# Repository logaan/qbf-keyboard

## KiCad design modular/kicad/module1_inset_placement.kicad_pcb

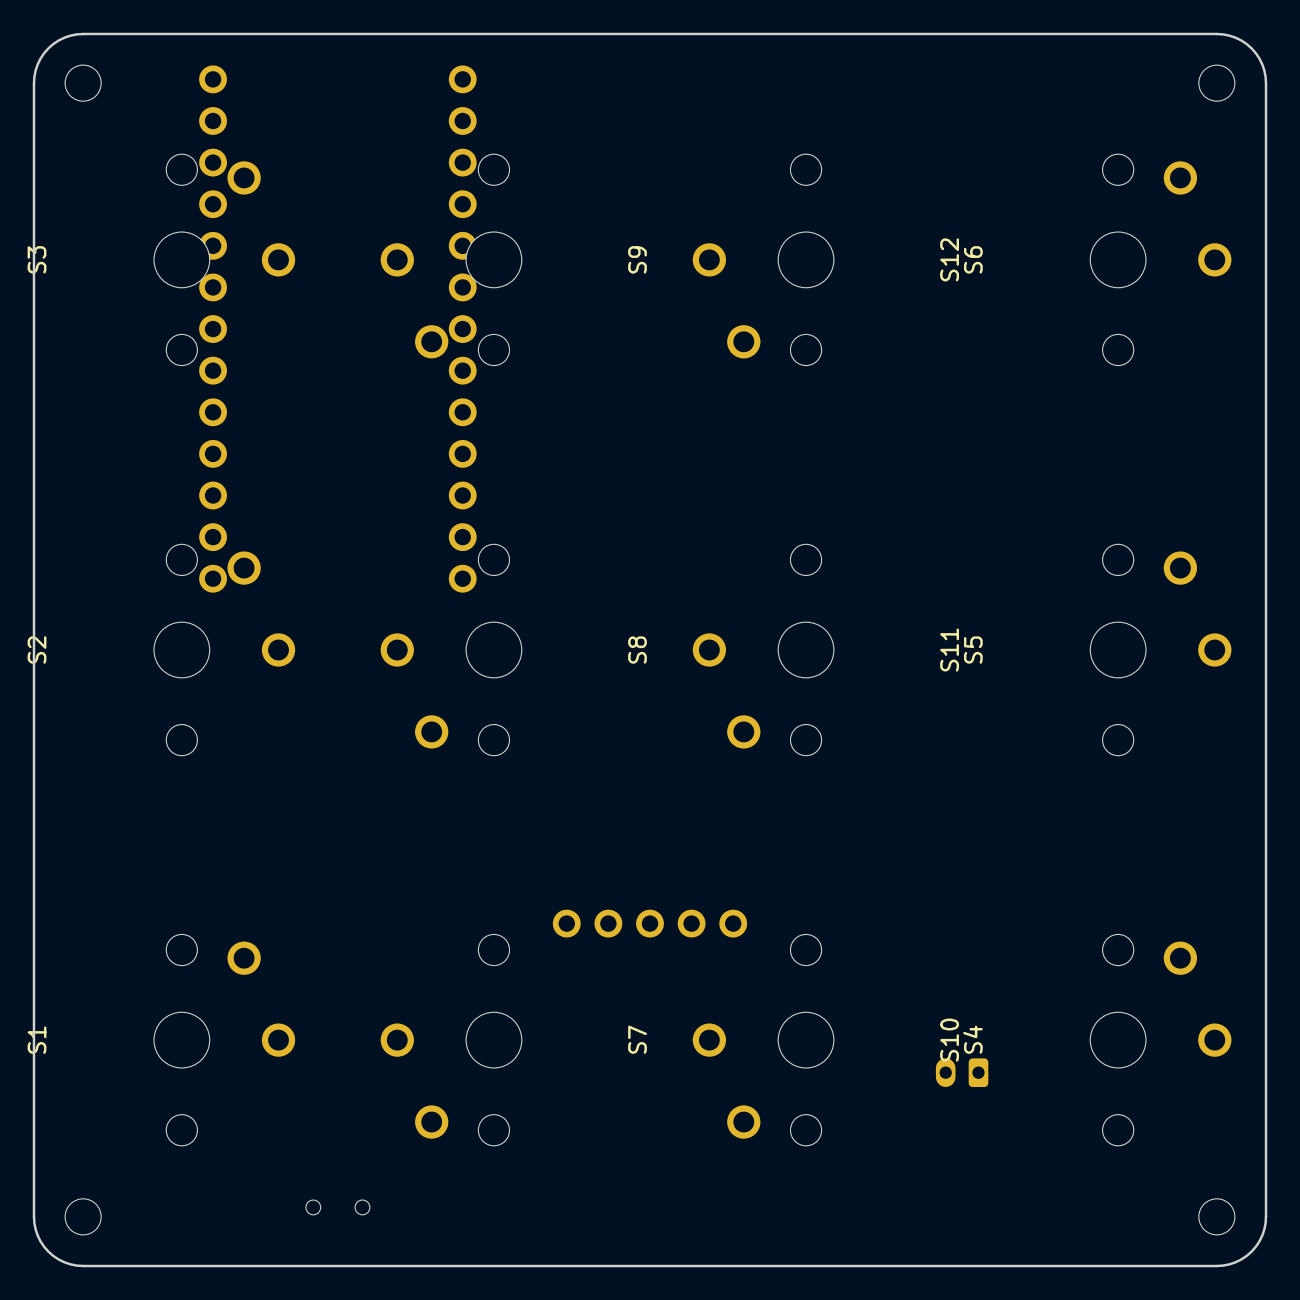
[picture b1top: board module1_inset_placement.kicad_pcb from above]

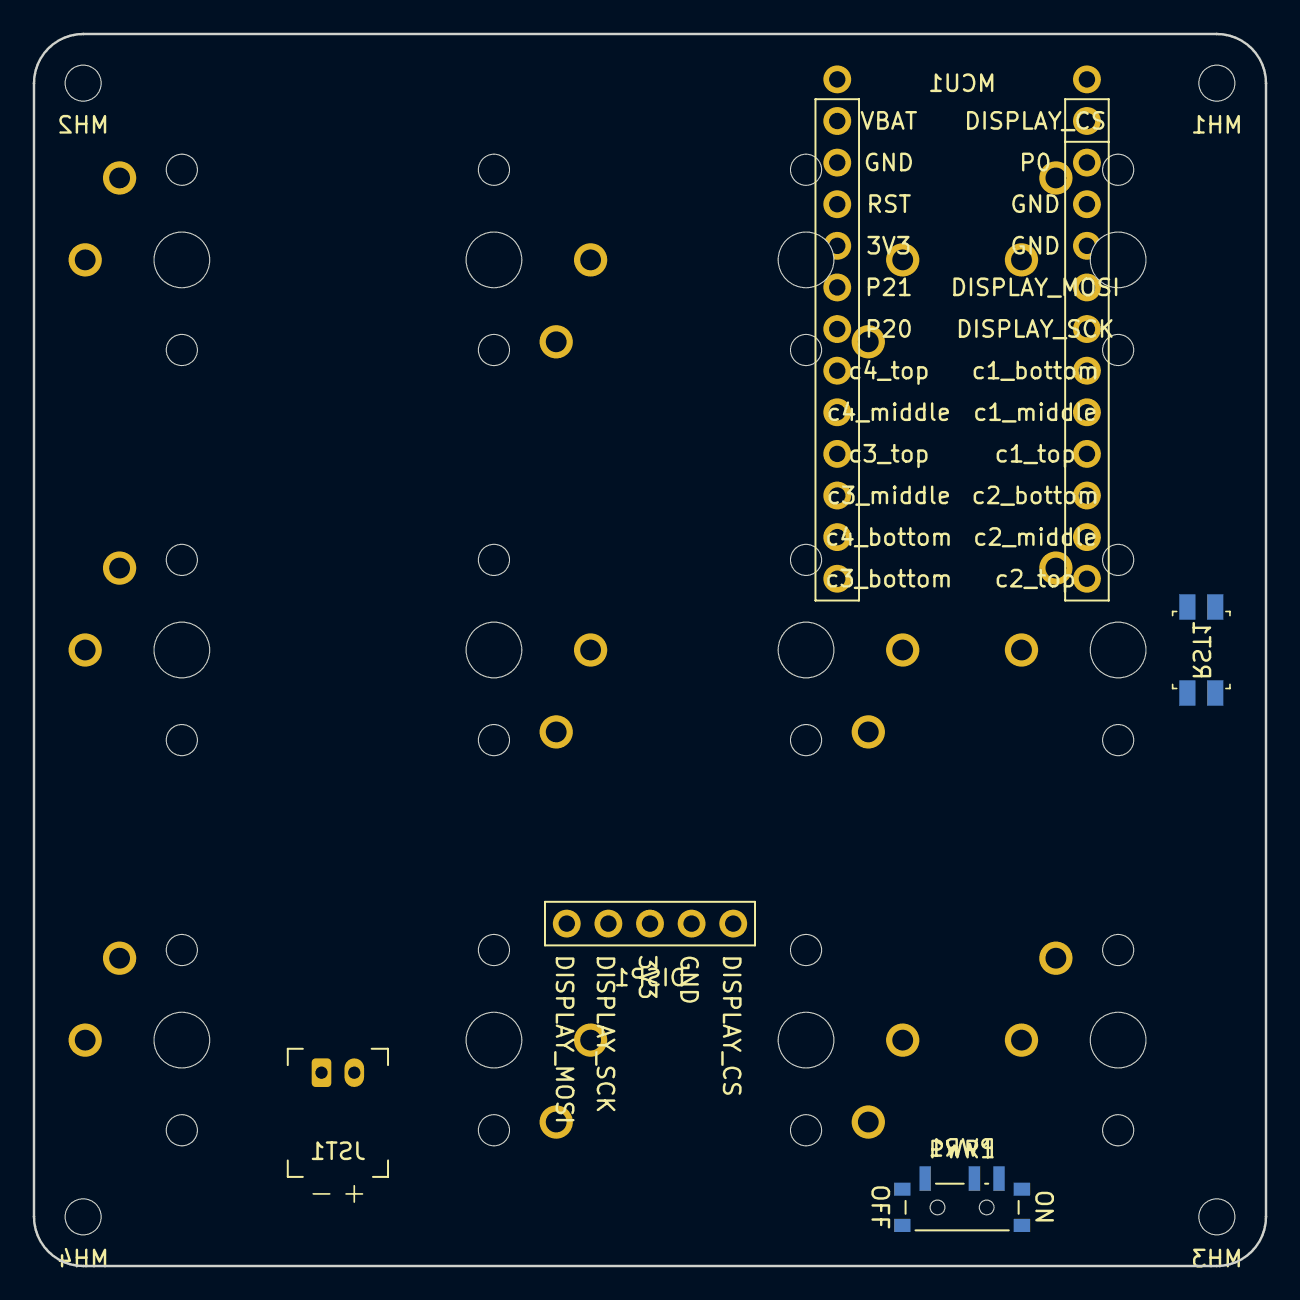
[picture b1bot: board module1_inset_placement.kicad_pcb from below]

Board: 2 copper layers, 75.2 x 75.2 mm, 21 parts (9 on the bottom side), 20 nets, no tracks yet.

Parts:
DISP1: display_nice_view
JST1: battery_connector_jst_ph_2
MCU1: mcu_nice_nano
MH1, MH2, MH3, MH4: mounting_hole_npth
PWR1: power_switch_smd_side
RST1: reset_switch_smd_side
S1, S2, S3, S4, S5, S6, S7, S8, S9, S10, S11, S12: switch_choc_v1_v2

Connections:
3V3: DISP1.3, MCU1.4
BAT_P: JST1.2, PWR1.3
DISPLAY_CS: DISP1.1, MCU1.24
DISPLAY_MOSI: DISP1.5, MCU1.20
DISPLAY_SCK: DISP1.4, MCU1.19
GND: DISP1.2, JST1.1, MCU1.2, MCU1.21, MCU1.22, MCU1.25, RST1.1, RST1.3, S1.1, S2.1, S3.1, S4.1, S5.1, S6.1, S7.1, S8.1, S9.1, S10.1, S11.1, S12.1
RST: MCU1.3, RST1.2, RST1.4
VBAT: MCU1.1, MCU1.26, PWR1.2
c1_bottom: MCU1.18, S1.2
c1_middle: MCU1.17, S2.2
c1_top: MCU1.16, S3.2
c2_bottom: MCU1.15, S7.2
c2_middle: MCU1.14, S8.2
c2_top: MCU1.13, S9.2
c3_bottom: MCU1.12, S10.2
c3_middle: MCU1.10, S11.2
c3_top: MCU1.9, S12.2
c4_bottom: MCU1.11, S4.2
c4_middle: MCU1.8, S5.2
c4_top: MCU1.7, S6.2

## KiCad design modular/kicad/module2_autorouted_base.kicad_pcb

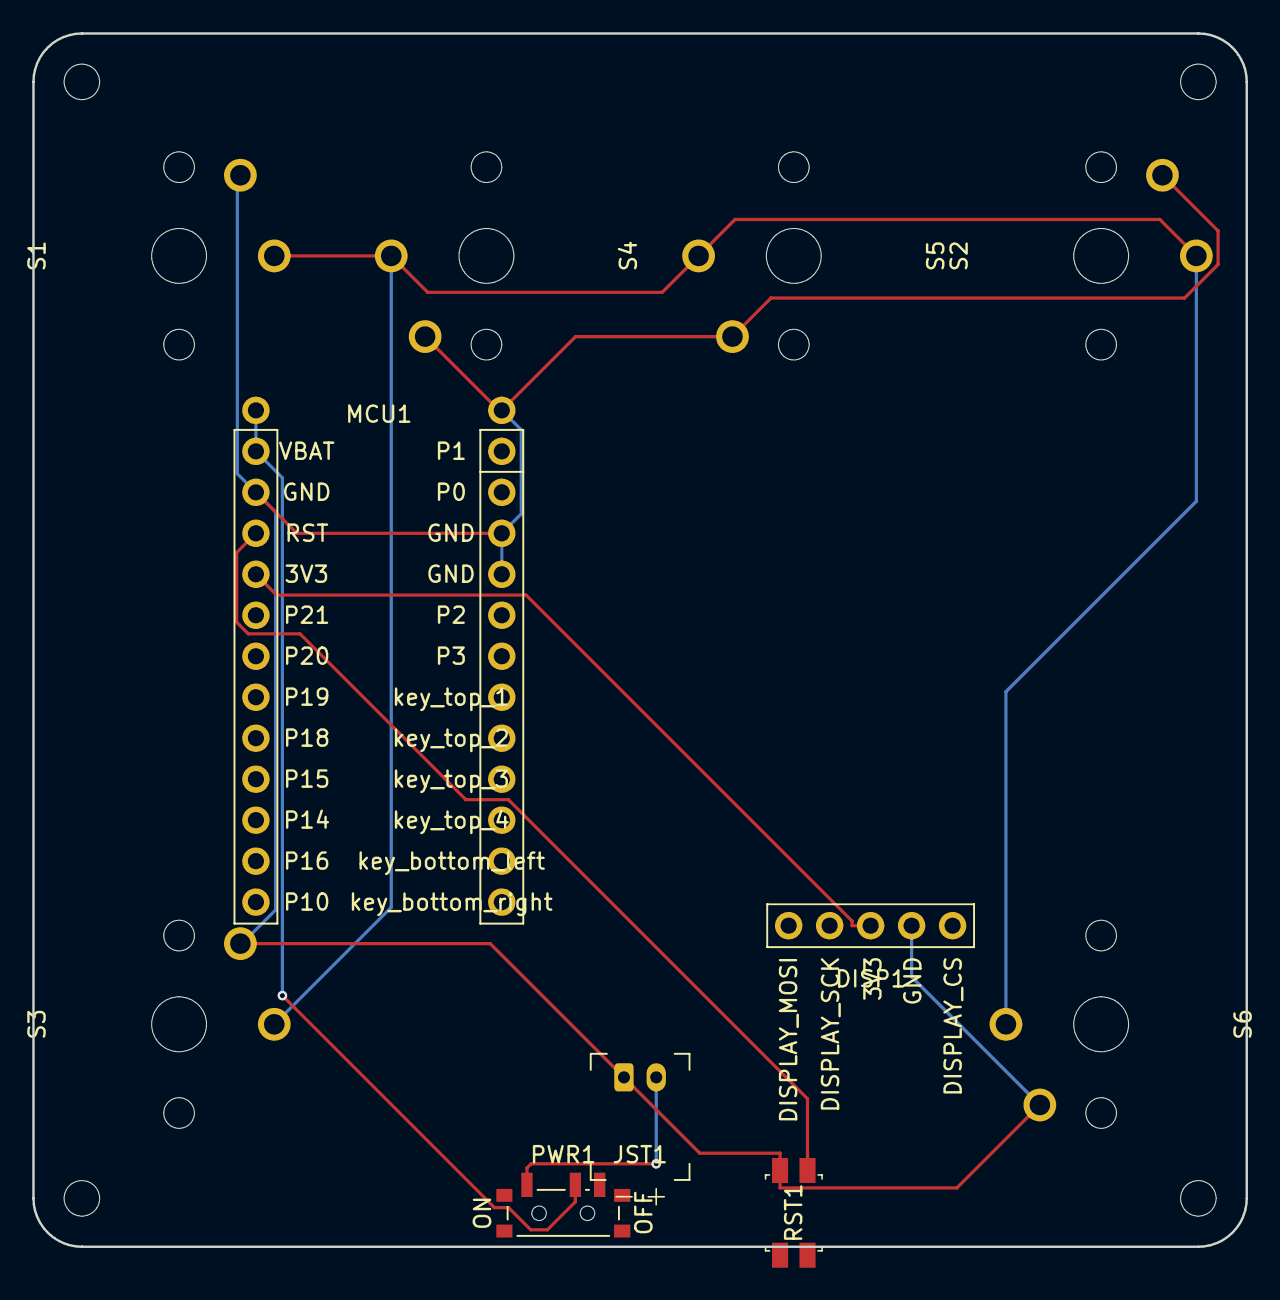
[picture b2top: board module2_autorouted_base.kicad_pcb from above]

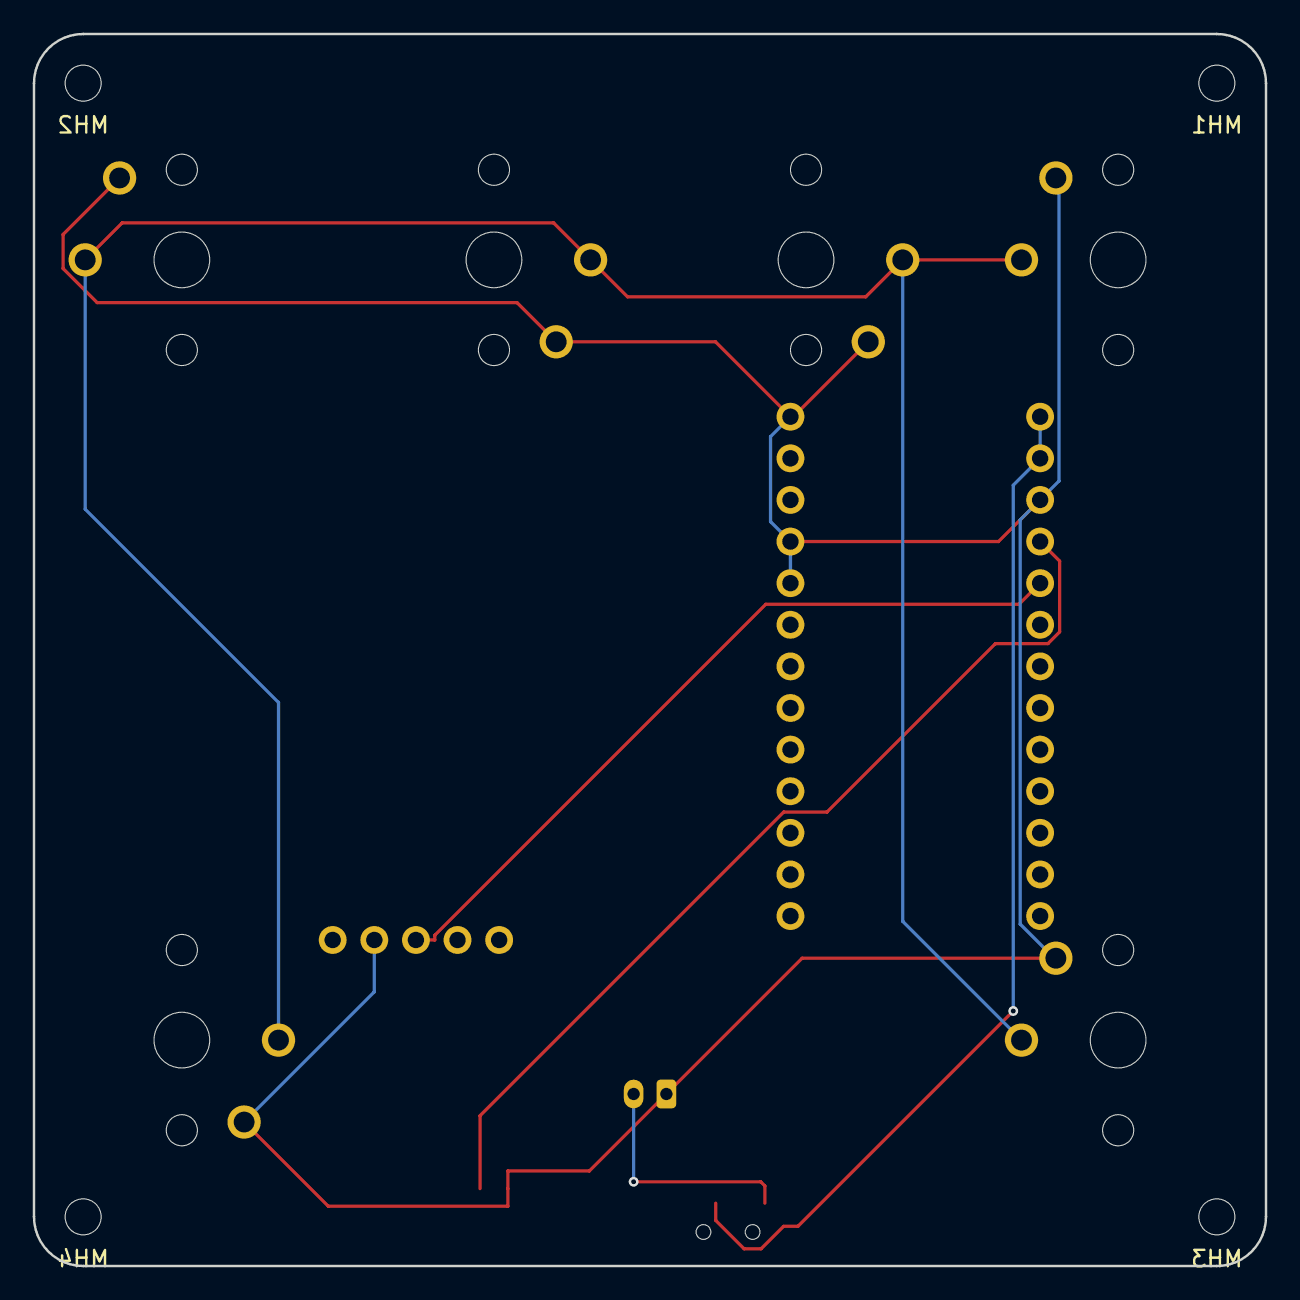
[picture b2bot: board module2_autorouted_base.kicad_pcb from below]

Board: 2 copper layers, 75.2 x 75.2 mm, 15 parts (4 on the bottom side), 6 nets.

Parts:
DISP1: display_nice_view
JST1: battery_connector_jst_ph_2
MCU1: mcu_nice_nano
MH1, MH2, MH3, MH4: mounting_hole_npth
PWR1: power_switch_smd_side
RST1: reset_switch_smd_side
S1, S2, S3, S4, S5, S6: switch_choc_v1_v2

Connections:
3V3: DISP1.3, MCU1.21
BAT_P: JST1.2, PWR1.1
GND: DISP1.4, JST1.1, MCU1.3, MCU1.4, MCU1.23, MCU1.26, RST1.1, RST1.3, S1.1, S2.1, S3.1, S4.1, S5.1, S6.1
RST: MCU1.22, RST1.2, RST1.4
VBAT: MCU1.24, MCU1.25, PWR1.2
default_default: S1.2, S2.2, S3.2, S4.2, S5.2, S6.2
